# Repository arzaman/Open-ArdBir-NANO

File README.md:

# Open-ArdBir-NANO
Repository for HW design file (PCB, schematic)  of ArdBir board based on arduino NANO version

Open Ardbir is an open source SW (up to release 2.8.3) to control and automate beer brewing process
The SW have been developed based on Arduino UNO board (Atmega328 MCU) with few surroundings HW component to drive and interface external element (PUMP, Heating element , LCD, push button etc.)

There are few open source HW board available supporting the SW either designed as  shield on top of Arduino Board or stand alone board (all in one board)

In the repository you can find my personal design of a board based on Arduino NANO V3 version with few additional features (not all supported by current SW version)

•	2 x DB18B20 temp probe

•	2 x 12v SSR/Relay out

•	2 x 12V power out (3A) 

•	Push button/LED/buzzer

The mapping of pinout is completely compatible with all other version (1 x DS18B20,SSR,PUM) while the second set of input is for future applications
The 12V power output can drive directly small pump (like solar project) and/or solenoid valve

The board has been designed in a very compact size to be mounted front panel

•	double side PCB

•	Trough Hole Component

•	No SMD

Two version of PCB are available depending on the LCD mounting

•	LCD solder side: the LCD is mounted on the copper side leaving the components accessible

•	LCD on component side : LCD is mounted on the same side of components 

In the repository you can find two folders, one for each version, containing PCB and schematic in eagle forma and BoM

![Alt text] (https://github.com/arzaman/Open-ArdBir-NANO/blob/master/LCD-solder-side/ArdBir%20NANO%20schematic.png)

Enjoy and feel free to modify/fork the project

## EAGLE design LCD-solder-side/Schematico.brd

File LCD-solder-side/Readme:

File for the PCB version with LCD mounted copper side

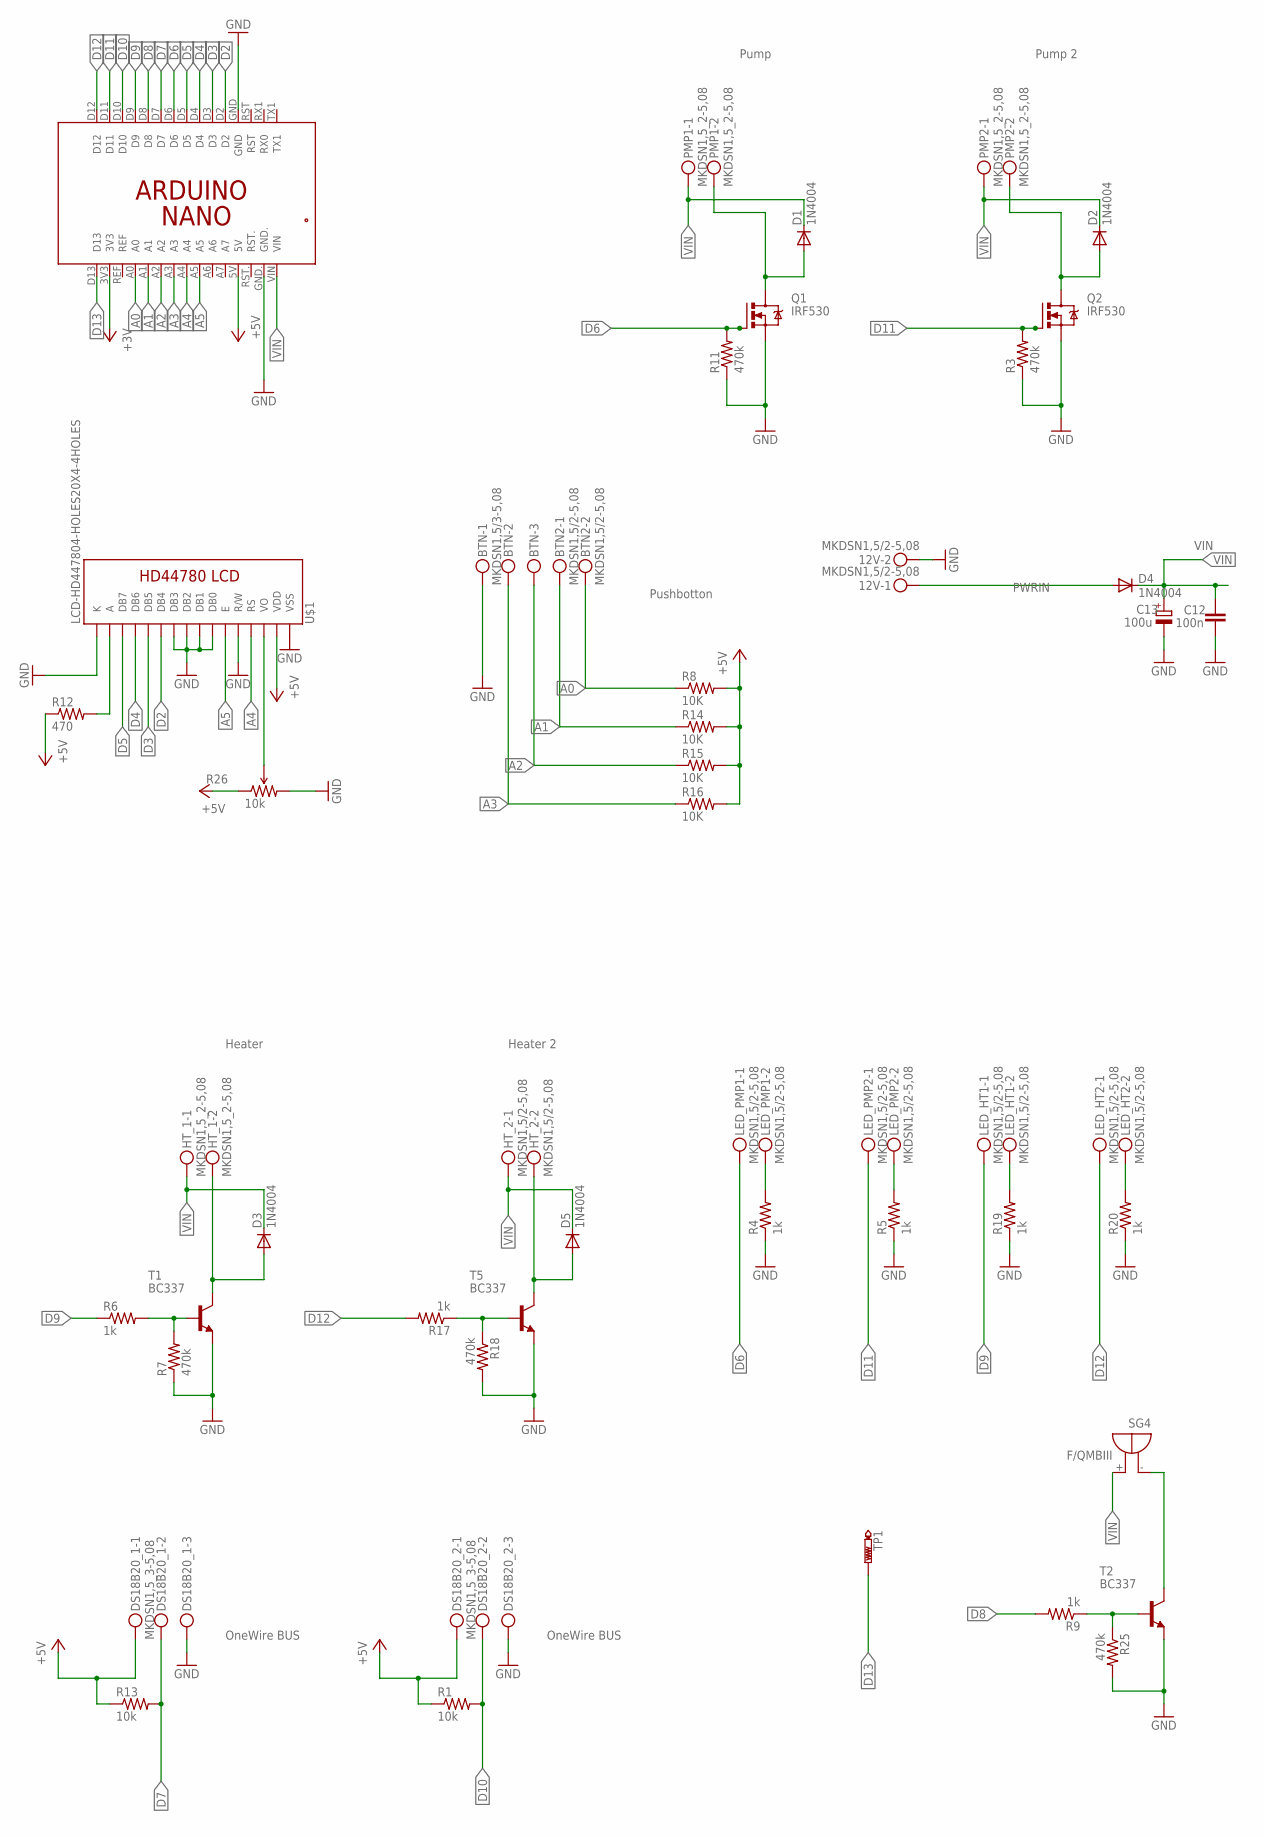
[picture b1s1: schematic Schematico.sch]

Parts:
12V: MKDSN1,5/2-5,08
BTN: MKDSN1,5/3-5,08
BTN2: MKDSN1,5/2-5,08
C12: 100n; C050-024X044
C13: 100u; TT5D6
D1, D2, D3, D4, D5: 1N4004; DO41-10
DS18B20_1, DS18B20_2: MKDSN1,5_3-5,08; MKDSN1,5-3-5,08
HT_1: MKDSN1,5_2-5,08; MKDSN1,5-2-5,08
HT_2: MKDSN1,5/2-5,08
LED_HT1, LED_HT2: MKDSN1,5/2-5,08
LED_PMP1, LED_PMP2: MKDSN1,5/2-5,08
PCB1: ARDUINO_NANO
PMP1, PMP2: MKDSN1,5_2-5,08; MKDSN1,5-2-5,08
Q1, Q2: IRF530; TO220BV
R1, R13: 10k; 0207/10
R3, R7, R11, R18, R25: 470k; 0207/10
R4, R5, R6, R9, R17, R19, R20: 1k; 0207/10
R8, R14, R15, R16: 10K; 0207/10
R12: 470; 0207/10
R26: 10k; 3362U-2
SG4: F/QMBIII
T1, T2, T5: BC337; TO92
TP1: PTR1PAD1-20; P1-20
U$1: LCD-HD447804-HOLES20X4-4HOLES; LCD-20X4-4HOLES

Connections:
+3V: PCB1.3V3
+5V: DS18B20_1.1, DS18B20_2.1, PCB1.5V, R1.1, R8.2, R12.1, R13.1, R14.2, R15.2, R16.2, R26.1 (CCW), U$1.P$2 (VDD)
A0: BTN2.2, PCB1.A0, R8.1
A1: BTN2.1, PCB1.A1, R14.1
A2: BTN.3, PCB1.A2, R15.1
A3: BTN.2, PCB1.A3, R16.1
A4: PCB1.A4, U$1.P$4 (RS)
A5: PCB1.A5, U$1.P$6 (E)
D2: PCB1.D2, U$1.P$11 (DB4)
D3: PCB1.D3, U$1.P$12 (DB5)
D4: PCB1.D4, U$1.P$13 (DB6)
D5: PCB1.D5, U$1.P$14 (DB7)
D6: LED_PMP1.1, PCB1.D6, Q1.G, R11.2
D7: DS18B20_1.2, PCB1.D7, R13.2
D8: PCB1.D8, R9.2
D9: LED_HT1.1, PCB1.D9, R6.1
D10: DS18B20_2.2, PCB1.D10, R1.2
D11: LED_PMP2.1, PCB1.D11, Q2.G, R3.2
D12: LED_HT2.1, PCB1.D12, R17.2
D13: PCB1.D13, TP1.TP
GND: 12V.2, BTN.1, C12.1, C13.-, DS18B20_1.3, DS18B20_2.3, PCB1.GND, PCB1.GND., Q1.S, Q2.S, R3.1, R4.1, R5.1, R7.1, R11.1, R18.2, R19.1, R20.1, R25.2, R26.3 (CW), T1.1 (E), T2.1 (E), T5.1 (E), U$1.P$1 (VSS), U$1.P$5 (R/W), U$1.P$7 (DB0), U$1.P$8 (DB1), U$1.P$9 (DB2), U$1.P$10 (DB3), U$1.P$16 (K)
unnamed: D2.A, PMP2.2, Q2.D
unnamed: LED_PMP1.2, R4.2
unnamed: LED_PMP2.2, R5.2
unnamed: D1.A, PMP1.2, Q1.D
unnamed: SG4.- (+), T2.3 (C)
unnamed: R9.1, R25.1, T2.2 (B)
unnamed: R12.2, U$1.P$15 (A)
unnamed: D3.A, HT_1.2, T1.3 (C)
unnamed: R26.2 (WIPER), U$1.P$3 (VO)
unnamed: R6.2, R7.2, T1.2 (B)
unnamed: D5.A, HT_2.2, T5.3 (C)
unnamed: R17.1, R18.1, T5.2 (B)
unnamed: LED_HT1.2, R19.2
unnamed: LED_HT2.2, R20.2
PWRIN: 12V.1, D4.A
VIN: C12.2, C13.+, D1.C, D2.C, D3.C, D4.C, D5.C, HT_1.1, HT_2.1, PCB1.VIN, PMP1.1, PMP2.1, SG4.+ (-)

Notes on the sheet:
OneWire BUS
Pump
Pump 2
Heater
Pushbotton
Heater 2

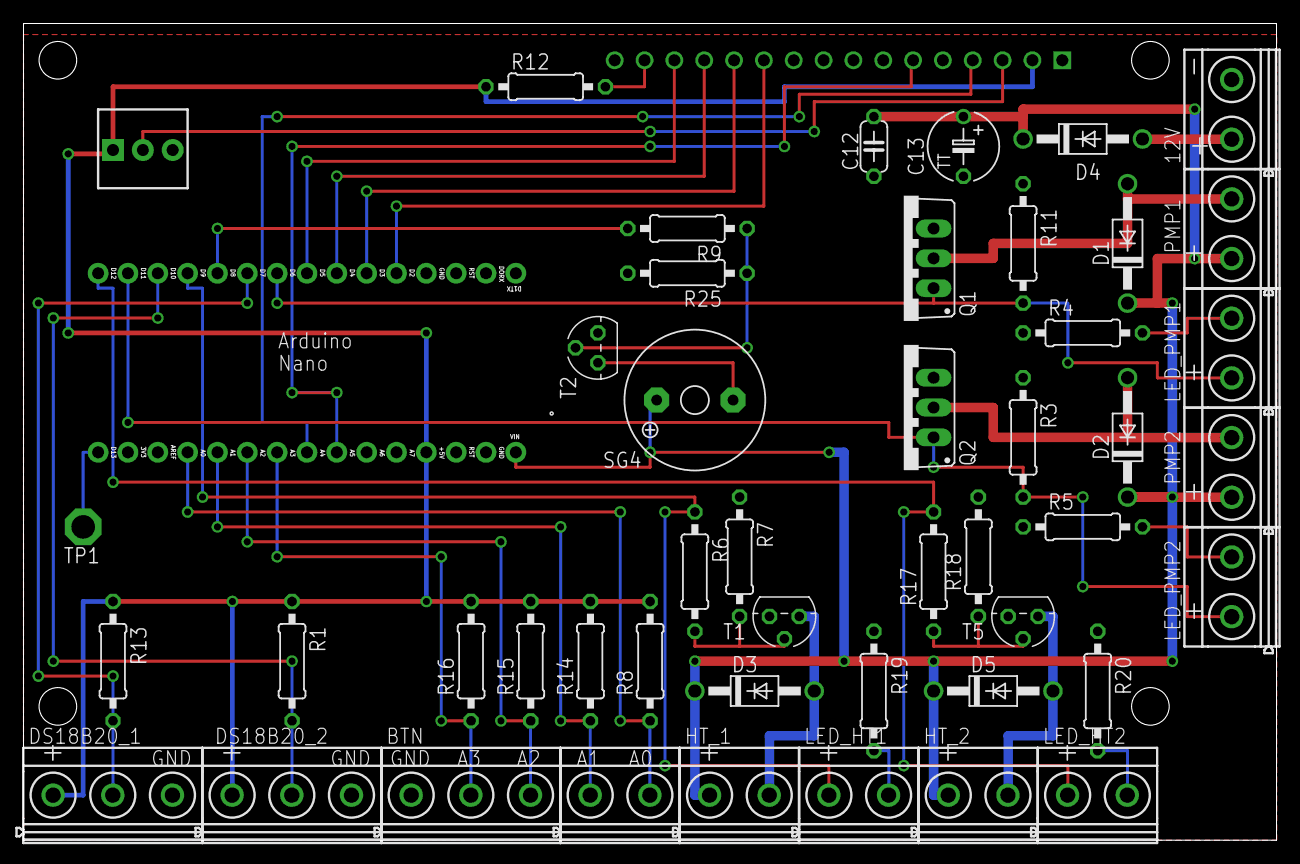
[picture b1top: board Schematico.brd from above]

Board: 2 copper layers, 106.7 x 69.5 mm, 49 parts (1 on the bottom side), 36 nets.

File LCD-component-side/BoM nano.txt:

Partlist

Exported from Schematico.sch at 11/12/2015 08:53

EAGLE Version 7.3.0 Copyright (c) 1988-2015 CadSoft

Assembly variant: 

Part      Value                         Device                        Package         Library                    Sheet

12V       MKDSN1,5/2-5,08               MKDSN1,5/2-5,08               MKDSN1,5/2-5,08 con-phoenix-508            1
BTN       MKDSN1,5/3-5,08               MKDSN1,5/3-5,08               MKDSN1,5/3-5,08 con-phoenix-508            1
BTN2      MKDSN1,5/2-5,08               MKDSN1,5/2-5,08               MKDSN1,5/2-5,08 con-phoenix-508            1
C12       100n                          C-EU050-024X044               C050-024X044    rcl                        1
C13       100u                          CPOL-EUTT6D6                  TT5D6           rcl                        1
D1        1N4004                        1N4004                        DO41-10         diode                      1
D2        1N4004                        1N4004                        DO41-10         diode                      1
D3        1N4004                        1N4004                        DO41-10         diode                      1
D4        1N4004                        1N4004                        DO41-10         diode                      1
D5        1N4004                        1N4004                        DO41-10         diode                      1
DS18B20_1 MKDSN1,5_3-5,08               MKDSN1,5_3-5,08               MKDSN1,5-3-5,08 con-phoenix-508            1
DS18B20_2 MKDSN1,5_3-5,08               MKDSN1,5_3-5,08               MKDSN1,5-3-5,08 con-phoenix-508            1
HT_1      MKDSN1,5_2-5,08               MKDSN1,5_2-5,08               MKDSN1,5-2-5,08 con-phoenix-508            1
HT_2      MKDSN1,5/2-5,08               MKDSN1,5/2-5,08               MKDSN1,5/2-5,08 con-phoenix-508            1
LED_HT1   MKDSN1,5/2-5,08               MKDSN1,5/2-5,08               MKDSN1,5/2-5,08 con-phoenix-508            1
LED_HT2   MKDSN1,5/2-5,08               MKDSN1,5/2-5,08               MKDSN1,5/2-5,08 con-phoenix-508            1
LED_PMP1  MKDSN1,5/2-5,08               MKDSN1,5/2-5,08               MKDSN1,5/2-5,08 con-phoenix-508            1
LED_PMP2  MKDSN1,5/2-5,08               MKDSN1,5/2-5,08               MKDSN1,5/2-5,08 con-phoenix-508            1
PCB1      ARDUINO_NANO                  ARDUINO_NANO                  ARDUINO_NANO    E14_Arduino_revB           1
PMP1      MKDSN1,5_2-5,08               MKDSN1,5_2-5,08               MKDSN1,5-2-5,08 con-phoenix-508            1
PMP2      MKDSN1,5_2-5,08               MKDSN1,5_2-5,08               MKDSN1,5-2-5,08 con-phoenix-508            1
Q1        IRF530                        IRF530                        TO220BV         transistor-power           1
Q2        IRF530                        IRF530                        TO220BV         transistor-power           1
R1        10k                           R-US_0207/10                  0207/10         resistor                   1
R3        470k                          R-US_0207/10                  0207/10         resistor                   1
R4        1k                            R-US_0207/10                  0207/10         resistor                   1
R5        1k                            R-US_0207/10                  0207/10         resistor                   1
R6        1k                            R-US_0207/10                  0207/10         resistor                   1
R7        470k                          R-US_0207/10                  0207/10         resistor                   1
R8        10K                           R-US_0207/10                  0207/10         resistor                   1
R9        1k                            R-US_0207/10                  0207/10         resistor                   1
R11       470k                          R-US_0207/10                  0207/10         resistor                   1
R12       470                           R-US_0207/10                  0207/10         resistor                   1
R13       10k                           R-US_0207/10                  0207/10         resistor                   1
R14       10K                           R-US_0207/10                  0207/10         resistor                   1
R15       10K                           R-US_0207/10                  0207/10         resistor                   1
R16       10K                           R-US_0207/10                  0207/10         resistor                   1
R17       1k                            R-US_0207/10                  0207/10         resistor                   1
R18       470k                          R-US_0207/10                  0207/10         resistor                   1
R19       1k                            R-US_0207/10                  0207/10         resistor                   1
R20       1k                            R-US_0207/10                  0207/10         resistor                   1
R25       470k                          R-US_0207/10                  0207/10         resistor                   1
R26       10k                           TRIMPOT3362U-2                3362U-2         SparkFun-Electromechanical 1
SG4       F/QMBIII                      F/QMBIII                      F/QMBIII        buzzer                     1
T1        BC337                         BC337                         TO92            transistor-neu-to92        1
T2        BC337                         BC337                         TO92            transistor-neu-to92        1
T5        BC337                         BC337                         TO92            transistor-neu-to92        1
TP1       PTR1PAD1-20                   PTR1PAD1-20                   P1-20           testpad                    1
U$1       LCD-HD447804-HOLES20X4-4HOLES LCD-HD447804-HOLES20X4-4HOLES LCD-20X4-4HOLES HD44780LCD                 1

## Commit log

2015-12-22 ardbir nano
2015-12-22 summary

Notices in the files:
parts and their libraries:
SparkFun-Electromechanical: Licensing: Creative Commons ShareAlike 4.0 International - https://creativecommons.org/licenses/by-sa/4.0
